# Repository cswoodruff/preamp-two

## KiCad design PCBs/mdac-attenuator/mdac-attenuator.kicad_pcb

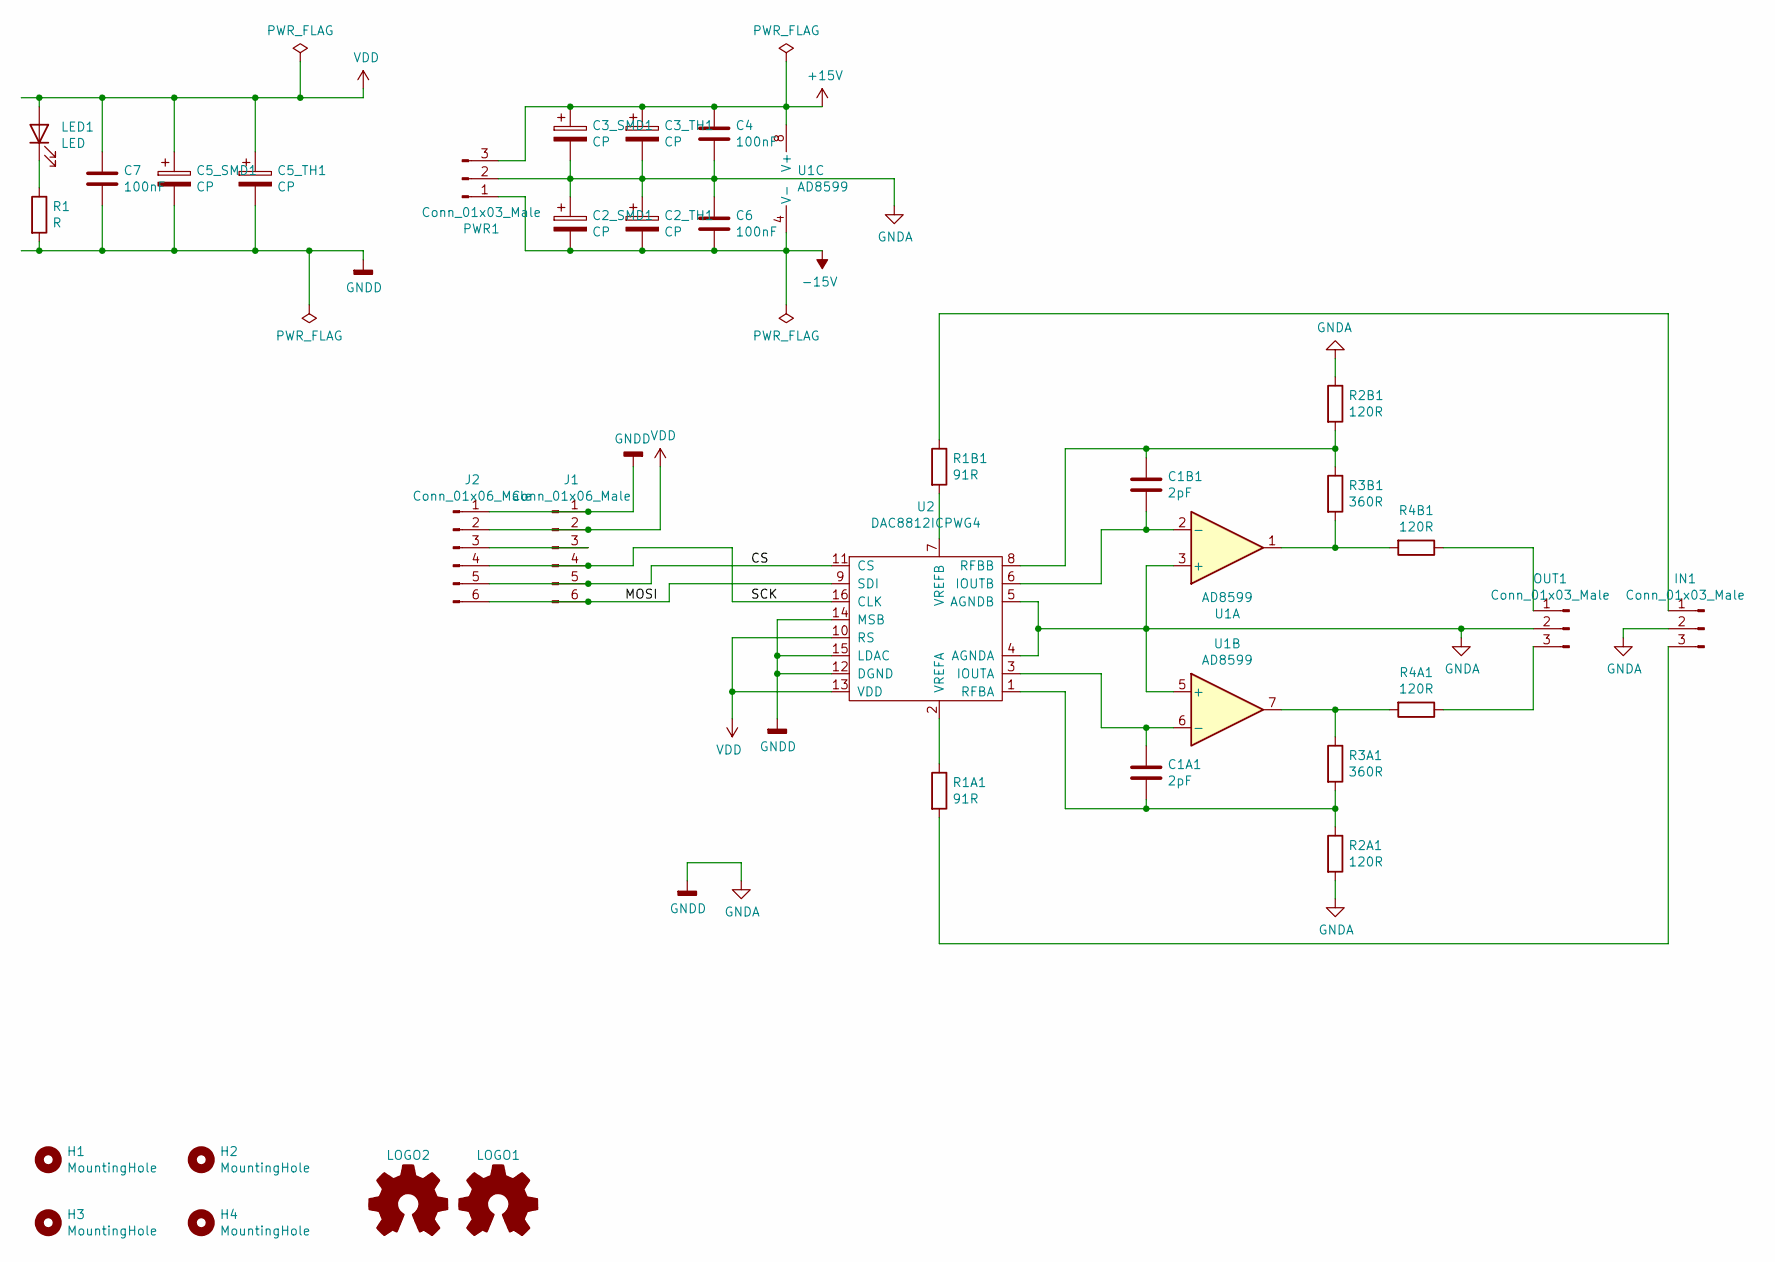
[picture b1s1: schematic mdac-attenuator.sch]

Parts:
C1A1, C1B1: 2pF; C_0805_2012Metric_Pad1.15x1.40mm_HandSolder
C2_SMD1, C3_SMD1, C5_SMD1: CP; CP_Elec_8x10
C2_TH1, C3_TH1, C5_TH1: CP; CP_Radial_D10.0mm_P5.00mm
C4, C6, C7: 100nF; C_1206_3216Metric_Pad1.42x1.75mm_HandSolder
H1, H2, H3, H4: MountingHole; MountingHole_3.2mm_M3_DIN965
IN1: Conn_01x03_Male; Molex_KK-254_AE-6410-03A_1x03_P2.54mm_Vertical
J1: Conn_01x06_Male; Molex_KK-254_AE-6410-06A_1x06_P2.54mm_Vertical
J2: Conn_01x06_Male; PinHeader_1x06_P2.54mm_Vertical
LED1: LED; LED_1206_3216Metric
LOGO1, LOGO2: Logo_Open_Hardware_Small; OSHW-Logo_7.5x8mm_SilkScreen
OUT1: Conn_01x03_Male; Molex_KK-254_AE-6410-03A_1x03_P2.54mm_Vertical
PWR1: Conn_01x03_Male; Molex_KK-254_AE-6410-03A_1x03_P2.54mm_Vertical
R1: R; R_1206_3216Metric_Pad1.42x1.75mm_HandSolder
R1A1, R1B1: 91R; R_1206_3216Metric_Pad1.42x1.75mm_HandSolder
R2A1, R2B1, R4A1, R4B1: 120R; R_1206_3216Metric_Pad1.42x1.75mm_HandSolder
R3A1, R3B1: 360R; R_1206_3216Metric_Pad1.42x1.75mm_HandSolder
U1: AD8599; SOIC-8_3.9x4.9mm_P1.27mm
U2: DAC8812ICPWG4; TSSOP-16_4.4x5mm_P0.65mm

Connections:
+15V: C3_SMD1.1, C3_TH1.1, C4.1, PWR1.3, U1.8 (V+)
-15V: C2_SMD1.2, C2_TH1.2, C6.2, PWR1.1, U1.4 (V-)
/CS: J1.5, J2.5, U2.11 (CS)
/MOSI: J1.6, J2.6, U2.9 (SDI)
/SCK: J1.4, J2.4, U2.16 (CLK)
GNDA: C2_SMD1.1, C2_TH1.1, C3_SMD1.2, C3_TH1.2, C4.2, C5_SMD1.2, C5_TH1.2, C6.1, C7.2, IN1.2, J1.1, J2.1, OUT1.2, PWR1.2, R1.2, R2A1.2, R2B1.1, U1.3 (+), U1.5 (+), U2.4 (AGNDA), U2.5 (AGNDB), U2.12 (DGND), U2.14 (MSB), U2.15 (LDAC)
unnamed: C1A1.1, U1.6 (-), U2.3 (IOUTA)
unnamed: C1A1.2, R2A1.1, R3A1.2, U2.1 (RFBA)
unnamed: C1B1.1, R2B1.2, R3B1.1, U2.8 (RFBB)
unnamed: C1B1.2, U1.2 (-), U2.6 (IOUTB)
unnamed: IN1.1, R1B1.1
unnamed: IN1.3, R1A1.2
unnamed: J1.3, J2.3
unnamed: LED1.1 (K), R1.1
unnamed: OUT1.1, R4B1.1
unnamed: OUT1.3, R4A1.1
unnamed: R1A1.1, U2.2 (VREFA)
unnamed: R1B1.2, U2.7 (VREFB)
unnamed: R3A1.1, R4A1.2, U1.7
unnamed: R3B1.2, R4B1.2, U1.1
VDD: C5_SMD1.1, C5_TH1.1, C7.1, J1.2, J2.2, LED1.2 (A), U2.10 (RS), U2.13 (VDD)

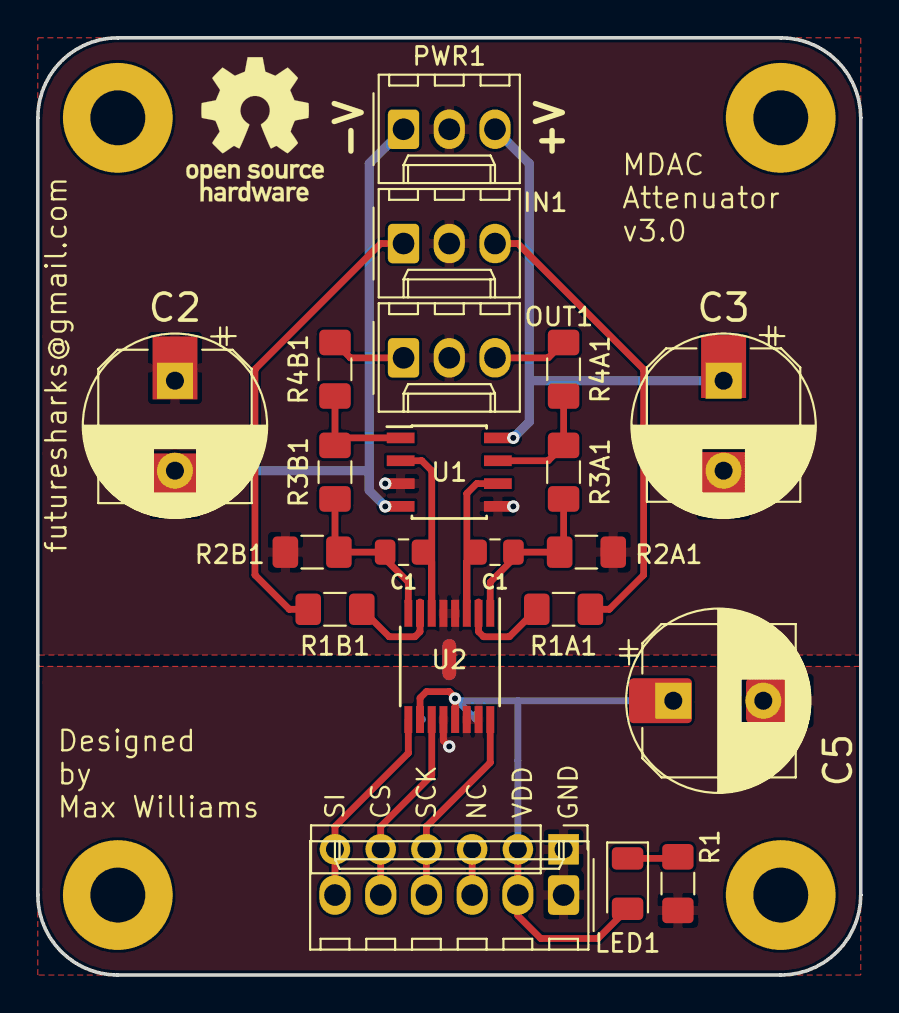
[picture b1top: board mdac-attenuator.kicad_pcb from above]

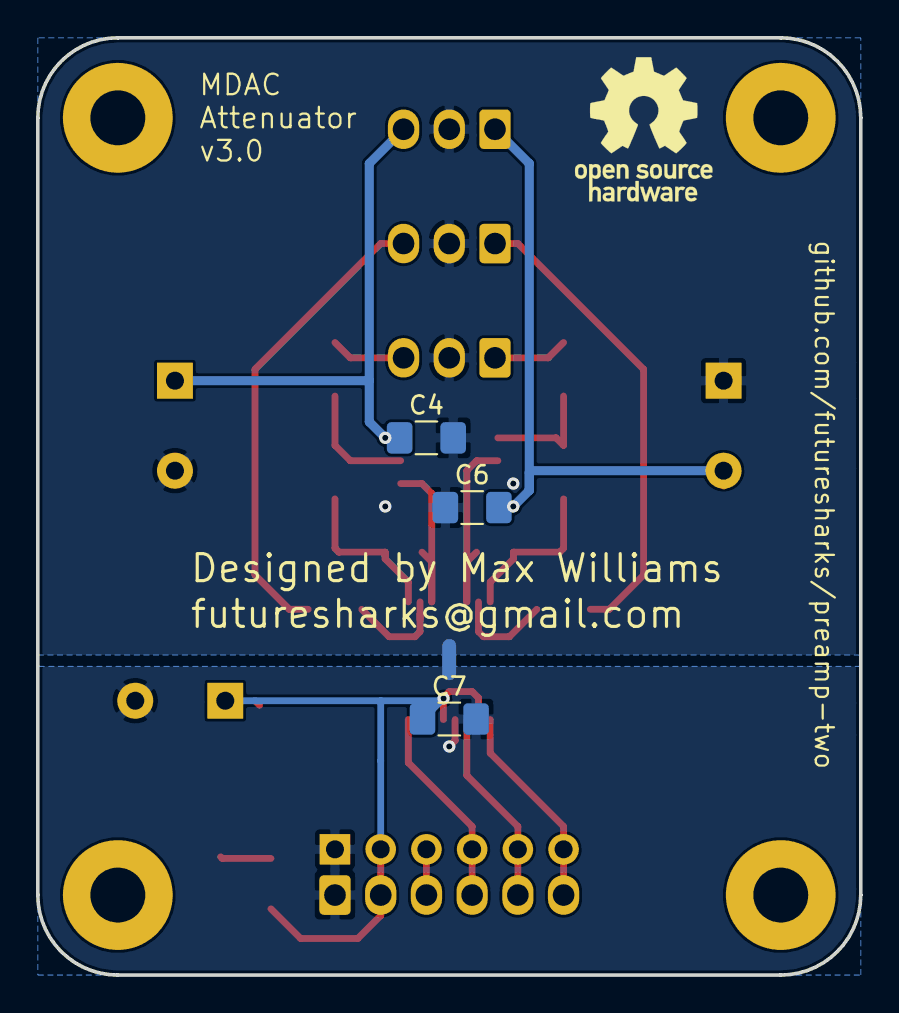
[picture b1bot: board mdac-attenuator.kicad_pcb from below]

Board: 2 copper layers, 45.7 x 52.1 mm, 34 parts (4 on the bottom side), 21 nets.

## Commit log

2021-08-28 Updated the mdac-attenuator to work with kicad 5.
